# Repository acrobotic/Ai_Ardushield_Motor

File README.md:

Overview
---
This repository includes the Eagle design files (schematics and layout) for our
[Motor Shield for the Arduino Uno][1]. The shield design is based on two ICs:
the Toshiba TB6612FNG dual motor driver and the NXP PCA9685 16-bit PWM
generator.  The TB6612FNG uses the PWM signals generated by the PCA9685 to set
the speed and direction of the motor(s) connected to its output.  The PWM
signals are set by the commands sent from the Arduino to the PCA9685
via I2C.

The shield includes 2 motor driver chips, so it's able to control up to 4
bi-directional DC motors, 2 stepper motors (uni- or bi-polar), or a combination
of the two types.  

The PWM chip is controlled via I2C, which allows the shield to be stackable.
By setting each shield on the stack to a different I2C address we can control
(in theory) up to 32 of these shields with a single Arduino.

A couple of standard 3-pin headers are readily available on the board for
connecting servo motors directly to pins D8 and D9 on the Arduino.

The firmware files along with code samples are also included in this
repository.

This product was heavily inspired by the [Adafruit Motor/Stepper/Servo Shield
for Arduino][2], and it's released under a (hopefully) compatible open-source
license detailed below.

Product page
---
Please consider buying products from Acrobotic to help fund future Open-Source
projects like this! We'll always put our best effort in every project, and
release all our design files and code for you to use.

[Tutorials, technical details, and more information about this product can be
found here: http://acrobotic.com/catalog/product/view/id/63][1]

License Information
---

All contents of this repository are licensed under a [Creative Commons
Attribution-ShareAlike 3.0 Unported
License](http://creativecommons.org/licenses/by-sa/3.0/).

[1]: http://acrobotic.com/catalog/product/view/id/63 "Ardushield Motor"
[2]: http://www.adafruit.com/products/1438 "Adafruit Motor/Stepper/Servo Shield for Arduino"

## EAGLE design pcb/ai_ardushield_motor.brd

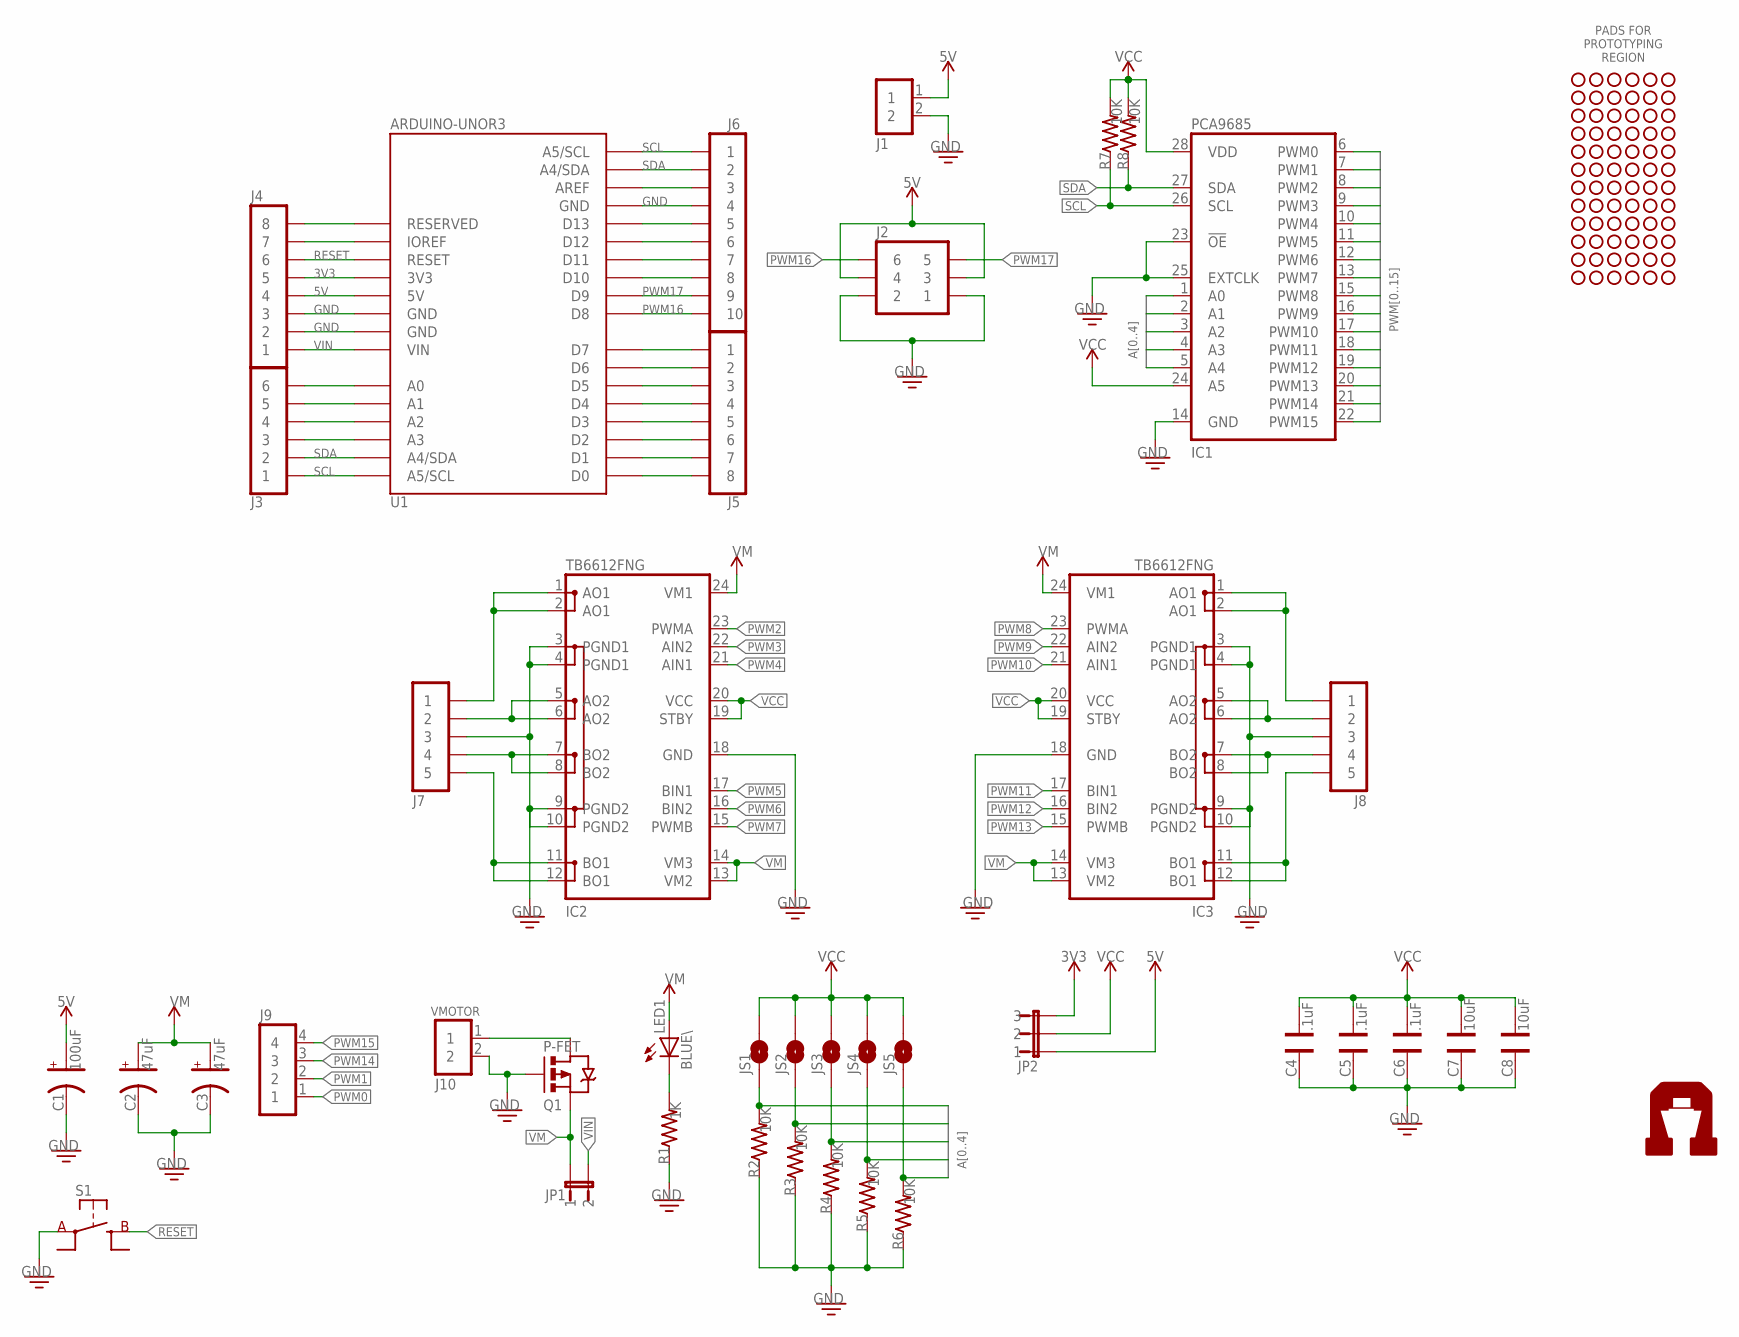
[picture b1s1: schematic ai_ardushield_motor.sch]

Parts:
C1: 100uF; CAP-PANASONIC-C
C2, C3: 47uF; CAP-PANASONIC-C
C4, C5, C6: .1uF; CAP-0603
C7, C8: 10uF; CAP-0603
IC1: PCA9685; TSSOP28
IC2, IC3: TB6612FNG; SSOP24
J1, J10: 1X02ST; 1X02-ST
J2: 2X03
J3: 1X06
J4, J5: 1X08
J6: 1X10
J7, J8: 1X05ST; 1X05-ST
J9: 1X04
J11, J12, J13, J14, J15, J16, J17, J18, J19, J20, J21, J22: 1X06-PROTO; 1X06-NOFIRST
JP1: 1X02-PJ; 1X02
JP2: 1X03-PJ; 1X03
JS1, JS2, JS3, JS4, JS5: 1X02-SJNO; 1X02-SJ-NO
LED1: BLUE\; LED-0603
Q1: P-FET; TO252
R1: 1K; RES-0603
R2, R3, R4, R5, R6, R7, R8: 10K; RES-0603
S1: SW-SPSTSMD06X06; SW-SPST-SMD06X06
U1: ARDUINOUNOR3; UNOR3
U$14: AI-LOGOL; AI-LOGO-L

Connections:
3V3: J4.5, JP2.3, U1.3V3
5V: C1.A, J1.1, J2.3, J2.4, J4.4, JP2.1, U1.5V
A0: IC1.1 (A0), JS1.1, R2.2
A1: IC1.2 (A1), JS2.1, R3.2
A2: IC1.3 (A2), JS3.1, R4.2
A3: IC1.4 (A3), JS4.1, R5.2
A4: IC1.5 (A4), JS5.1, R6.2
GND: C1.C, C2.C, C3.C, C4.2, C5.2, C6.2, C7.2, C8.2, IC1.14 (GND), IC1.23 (!OE), IC1.25 (EXTCLK), IC2.3 (PGND1), IC2.4 (PGND1), IC2.9 (PGND2), IC2.10 (PGND2), IC2.18 (GND), IC3.3 (PGND1), IC3.4 (PGND1), IC3.9 (PGND2), IC3.10 (PGND2), IC3.18 (GND), J1.2, J2.1, J2.2, J4.2, J4.3, J6.4, J7.3, J8.3, J10.2, Q1.G, R1.1, R2.1, R3.1, R4.1, R5.1, R6.1, S1.A@1 (A), S1.A@2 (A), U1.GND@1 (GND), U1.GND@2 (GND), U1.GND@3 (GND)
unnamed: J5.1, U1.D7
unnamed: J5.2, U1.D6
unnamed: LED1.C, R1.2
unnamed: J3.3, U1.A3
unnamed: J3.4, U1.A2
unnamed: J3.5, U1.A1
unnamed: J3.6, U1.A0
unnamed: J4.7, U1.IOREF
unnamed: J4.8, U1.RESERVED
unnamed: J5.3, U1.D5
unnamed: J5.4, U1.D4
unnamed: J5.5, U1.D3
unnamed: J5.6, U1.D2
unnamed: J5.7, U1.D1
unnamed: J5.8, U1.D0
unnamed: IC2.1 (AO1), IC2.2 (AO1), J7.1
unnamed: IC2.5 (AO2), IC2.6 (AO2), J7.2
unnamed: J6.3, U1.AREF
unnamed: J6.5, U1.D13
unnamed: J6.6, U1.D12
unnamed: J6.7, U1.D11
unnamed: J6.8, U1.D10
unnamed: IC2.7 (BO2), IC2.8 (BO2), J7.4
unnamed: IC2.11 (BO1), IC2.12 (BO1), J7.5
unnamed: IC3.1 (AO1), IC3.2 (AO1), J8.1
unnamed: IC3.5 (AO2), IC3.6 (AO2), J8.2
unnamed: IC3.7 (BO2), IC3.8 (BO2), J8.4
unnamed: IC3.11 (BO1), IC3.12 (BO1), J8.5
PWM0: IC1.6 (PWM0), J9.1
PWM1: IC1.7 (PWM1), J9.2
PWM2: IC1.8 (PWM2), IC2.23 (PWMA)
PWM3: IC1.9 (PWM3), IC2.22 (AIN2)
PWM4: IC1.10 (PWM4), IC2.21 (AIN1)
PWM5: IC1.11 (PWM5), IC2.17 (BIN1)
PWM6: IC1.12 (PWM6), IC2.16 (BIN2)
PWM7: IC1.13 (PWM7), IC2.15 (PWMB)
PWM8: IC1.15 (PWM8), IC3.23 (PWMA)
PWM9: IC1.16 (PWM9), IC3.22 (AIN2)
PWM10: IC1.17 (PWM10), IC3.21 (AIN1)
PWM11: IC1.18 (PWM11), IC3.17 (BIN1)
PWM12: IC1.19 (PWM12), IC3.16 (BIN2)
PWM13: IC1.20 (PWM13), IC3.15 (PWMB)
PWM14: IC1.21 (PWM14), J9.3
PWM15: IC1.22 (PWM15), J9.4
PWM16: J2.6, J6.10, U1.D8
PWM17: J2.5, J6.9, U1.D9
RESET: J4.6, S1.B@1 (B), S1.B@2 (B), U1.RESET
SCL: IC1.26 (SCL), J3.1, J6.1, R7.1, U1.A5/SCL@1 (A5/SCL), U1.A5/SCL@2 (A5/SCL)
SDA: IC1.27 (SDA), J3.2, J6.2, R8.1, U1.A4/SDA@1 (A4/SDA), U1.A4/SDA@2 (A4/SDA)
VCC: C4.1, C5.1, C6.1, C7.1, C8.1, IC1.24 (A5), IC1.28 (VDD), IC2.19 (STBY), IC2.20 (VCC), IC3.19 (STBY), IC3.20 (VCC), JP2.2, JS1.2, JS2.2, JS3.2, JS4.2, JS5.2, R7.2, R8.2
VIN: J4.1, JP1.2, U1.VIN
VM: C2.A, C3.A, IC2.13 (VM2), IC2.14 (VM3), IC2.24 (VM1), IC3.13 (VM2), IC3.14 (VM3), IC3.24 (VM1), JP1.1, LED1.A, Q1.S
VMOTOR: J10.1, Q1.D

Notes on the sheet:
VMOTOR
PADS FOR PROTOTYPING REGION

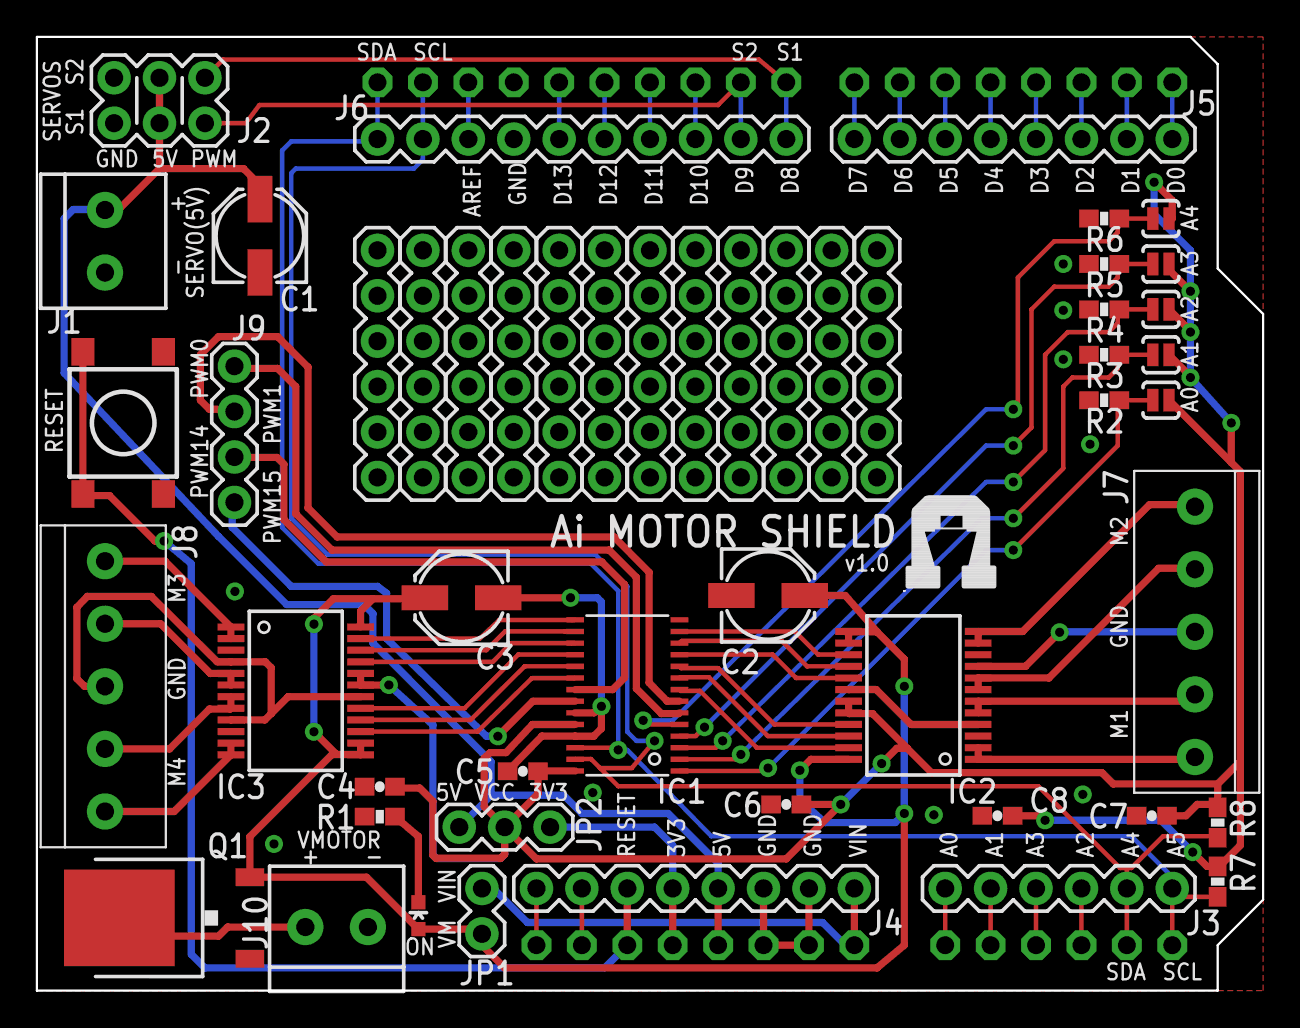
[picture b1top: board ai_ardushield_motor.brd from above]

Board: 2 copper layers, 68.6 x 53.3 mm, 53 parts (0 on the bottom side), 61 nets.

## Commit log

2013-07-25 First commit.
2013-07-25 Fixed a few minor warnings in the ERC.
2013-07-25 changed the pcb dimension width.
2013-10-06 New version including detailed BOM
2013-10-06 First commit to pages branch
2013-10-06 Modified README.md
2013-10-08 Fixed typo in BOM
2013-10-15 updated BOM and gerbers
2013-11-22 minor typo on BOM
2013-11-26 Updated to use latest libraries.
2013-11-26 updating schematic pdf
